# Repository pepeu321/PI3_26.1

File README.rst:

Controle de velocidade com telemetria e acionamento remoto da esteira transportadora do laboratório LPAE
#####################################################################

.. image:: imagens_principal/Esteira.png
   :width: 400px
   :align: center

.. contents::
   :local:
   :depth: 2

Visão geral
***********

Este projeto consiste no desenvolvimento de um sistema de controle de velocidade para uma esteira acionada por um motor DC, utilizando o microcontrolador ESP32. O sistema permite ao usuário definir a velocidade desejada pelo computador, enquanto um sensor realiza a medição da velocidade real do motor. Com base nessas informações, o controlador ajusta o sinal PWM aplicado ao motor, garantindo um controle preciso.

O projeto foi dividido em quatro etapas principais:

- `Etapa 1 <etapa_1/README.md>`_

Nesta etapa, foi realizado o estudo do microcontrolador ESP32, tipo do sensor que será utilizado, a comparação entre rampa de aceleração linear e rampa em S e o diagrama de blocos do sistema, permitindo a visualização geral do funcionamento do projeto.

- `Etapa 2 <etapa_2/README.rst>`_

Na Etapa 2, foram realizados testes individuais com os sensores que serão utilizados com o microcontrolador, e o desenvolvimento dos esquemáticos dos hardwares do sistema. 

- `Etapa 3 <etapa_3/README.rst>`_

Foi implementada a leitura do encoder utilizando o periférico PCNT corretamente, feito os layouts da PCI do driver que foi feito, foram desenvolvidos os firmwares responsáveis pelo acionamento do motor através do driver L298N e um programa preliminar para testar a comunicação COAP, além de fazer o projeto e implementação inicial de um controlador PID que será aplicado na esteira.

- `Etapa 4 <etapa_4/README.rst>`_

Por fim, na última etapa, foram integrados os módulos desenvolvidos nas etapas anteriores, incluindo a leitura do encoder, o acionamento do motor e a comunicação CoAP. Também foi implementado e ajustado o controlador PI, permitindo o controle de velocidade da esteira em malha fechada.
Além disso, foi desenvolvido um sistema de monitoramento remoto, capaz de definir a velocidade de referência e visualizar, em tempo real, a velocidade medida, o erro de controle, o duty cycle aplicado ao motor e o sentido de rotação.

Interface do usuário
********************

O controle remoto da esteira é realizado por uma aplicação desenvolvida em Python.

Os comandos disponíveis são:

- **on**
    Liga a esteira utilizando uma referência padrão.

- **off**
    Desliga a esteira.

- **rpm**
    Realiza uma única leitura da velocidade atual.

- **monitor**
    Exibe continuamente:

    - velocidade de referência;
    - velocidade medida;
    - erro de controle;
    - duty cycle aplicado;
    - sentido de rotação.

- **fwd**
    Define o sentido direto de rotação.

- **rev**
    Define o sentido reverso de rotação.

- **q**
    Encerra a aplicação

Diagrama de blocos do Sistema
********************

.. image:: imagens_principal/DiagramaBlocos.png
   :width: 700px
   :align: right

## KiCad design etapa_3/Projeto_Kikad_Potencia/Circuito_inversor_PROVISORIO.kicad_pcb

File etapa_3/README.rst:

Etapa 3
#######

.. contents::
   :local:
   :depth: 2

Visão geral
***********

Na Etapa 3, foram realizados 

📌 Projeto do controlador PID

📌 Implementação preliminar do controle PID no microcontrolador.

📌 Apresentação do gabinete desenvolvido em software 3D

📌 Layout da placa de potência

📌 Layout da placa de controle

📌 Teste de acionamento do motor

📌 Firmware preliminar com teste de comunicação COAP

Desenvolvimento
***************

Projeto do controlador PID
======

A primeira parte para o desenvolvimento do projeto de controle PID é a obtenção da planta do motor da esteira. Com a planta saberemos a resposta que o motor tem para uma resposta ao degrau, como é o comportamento da velocidade do motor(RPM) ao longo do tempo até atingir o regime permanente. 

Para obter a planta configuramos uma fonte de bancada com 12V e corrente limitada em 2A, depois disso é necessário conectar os pinos do encoder no esp32, como feito na etapa anterior. Com o encoder conectado ao esp32 é preciso gerar um sinal de degrau, e o degrau é gerado ligando a fonte de bancada. E para obter o gráfico da curva do rpm será preciso fazer as leituras do rpm através do esp, e então para cada instante de tempo amostrado e a leitura do rpm obtida será printada na tela. Depois copiamos esses valores para geração do gráfico no matlab.

O código anterior utilizado para medir o rpm com o encoder óptico estava certo para a configuração da etapa anterior, nesta etapa precisamos modificar o código da leitura do encoder porque no momento em que o rpm era amostrado também era printado na tela. E a função print tem um atraso, isso acarretava na perda de eventos. O rpm medido era defasado, então para velocidades que não variam até funciona, mas para obter uma curva é preciso retirar o print. E é o que foi feito.

Também foi retirada a função delay 100 ms, porque nós queremos ter uma precisão na leitura dos rpms. Para fazer isso foi necessário configurar um timer para contar até 100ms e quando chegar nesse período de tempo é gerado um sinal para calcular o rpm e armazenar em um vetor. Então depois de fazer a leitura, será printado o vetor de velocidades, com isso resolvemos o problema do print e também temos a precisão na leitura das amostras.

Então a diferença maior foi feita na main.c, o wheel.c e wheel.h não foram alterados. O código da main.c pode ser visto abaixo:

.. code-block:: c

	#include <stdio.h>
	
	#include "freertos/FreeRTOS.h"
	#include "freertos/task.h"
	
	#include "esp_log.h"
	#include "driver/gptimer.h"
	
	#include "wheel.h"
	
	static const char *TAG = "MAIN";
	
	#define PULSOS_POR_VOLTA 20
	
	#define TEMPO_TOTAL_MS     4000
	#define PERIODO_AMOSTRA_MS 100
	
	#define NUM_AMOSTRAS (TEMPO_TOTAL_MS / PERIODO_AMOSTRA_MS)
	
	static volatile bool sample_flag = false;

	// CALLBACK TIMER
	
	static bool timer_callback(
	    gptimer_handle_t timer,
	    const gptimer_alarm_event_data_t *edata,
	    void *user_ctx)
	{
	    sample_flag = true;
	    return false;
	}

	 //TIMER
	
	static gptimer_handle_t init_sample_timer(void)
	{
	    gptimer_handle_t timer = NULL;
	
	    gptimer_config_t timer_config = {
	        .clk_src = GPTIMER_CLK_SRC_DEFAULT,
	        .direction = GPTIMER_COUNT_UP,
	        .resolution_hz = 1000000,
	    };
	
	    ESP_ERROR_CHECK(
	        gptimer_new_timer(
	            &timer_config,
	            &timer));
	
	    gptimer_event_callbacks_t cbs = {
	        .on_alarm = timer_callback,
	    };
	
	    ESP_ERROR_CHECK(
	        gptimer_register_event_callbacks(
	            timer,
	            &cbs,
	            NULL));
	
	    gptimer_alarm_config_t alarm_config = {
	        .reload_count = 0,
	        .alarm_count = PERIODO_AMOSTRA_MS * 1000,
	        .flags = {
	            .auto_reload_on_alarm = true,
	        },
	    };
	
	    ESP_ERROR_CHECK(
	        gptimer_set_alarm_action(
	            timer,
	            &alarm_config));
	
	    ESP_ERROR_CHECK(gptimer_enable(timer));
	    ESP_ERROR_CHECK(gptimer_start(timer));
	
	    return timer;
	}

	// TASK AQUISICAO
	
	void task_aquisicao(void *pvParameters)
	{
	    wheel_Init();
	
	    int last_pulsos = 0;
	
	    float vetor_rpm[NUM_AMOSTRAS];
	
	    float rpm_filtrado = 0;
	
	    ESP_LOGI(TAG, "5 s");
	    vTaskDelay(pdMS_TO_TICKS(1000));
	
	    ESP_LOGI(TAG, "4 s");
	    vTaskDelay(pdMS_TO_TICKS(1000));
	
	    ESP_LOGI(TAG, "3 s");
	    vTaskDelay(pdMS_TO_TICKS(1000));
	
	    ESP_LOGI(TAG, "2 s");
	    vTaskDelay(pdMS_TO_TICKS(1000));
	
	    ESP_LOGI(TAG, "1 s");
	    vTaskDelay(pdMS_TO_TICKS(1000));
	
	    ESP_LOGI(TAG, "AGORA!");
	
	    gptimer_handle_t timer = init_sample_timer();
	
	    int n = 0;
	
	    while (n < NUM_AMOSTRAS)
	    {
	        if (sample_flag)
	        {
	            sample_flag = false;
	
	            int pulsos;
	
	            wheel_GetEncoderPulses(&pulsos);
	
	            int delta = pulsos - last_pulsos;
	
	            last_pulsos = pulsos;
	
	            float dt = PERIODO_AMOSTRA_MS / 1000.0f;
	
	            float rpm = (delta / (float)PULSOS_POR_VOLTA)* (60.0f / dt);
	
	            // filtro exponencial
	            rpm_filtrado =
	                0.7f * rpm_filtrado +
	                0.3f * rpm;
	
	            vetor_rpm[n] = rpm_filtrado;
	
	            n++;
	        }
	
	        vTaskDelay(pdMS_TO_TICKS(1));
	    }
	
	    ESP_ERROR_CHECK(gptimer_stop(timer));
	    ESP_ERROR_CHECK(gptimer_disable(timer));
	    ESP_ERROR_CHECK(gptimer_del_timer(timer));
	
	    ESP_LOGI(TAG, "Fim da aquisicao");
	
	    // CSV
	    printf("\n");
	    printf("tempo,rpm\n");
	
	    for (int i = 0; i < NUM_AMOSTRAS; i++)
	    {
	        float tempo =
	            i * (PERIODO_AMOSTRA_MS / 1000.0f);
	
	        printf("%.2f,%.2f\n",
	               tempo,
	               vetor_rpm[i]);
	    }
	
	    vTaskDelete(NULL);
	}

	void app_main(void)
	{
	    ESP_LOGI(TAG, "Sistema iniciado");
	
	    xTaskCreate(
	        task_aquisicao,
	        "task_aquisicao",
	        4096,
	        NULL,
	        5,
	        NULL);
	}

Os destaques para esse código são o tempo total de leitura, 4s, o que é mais do que suficiente para o motor atingir o regime permanente e o início da leitura é informado na tela para gerar o degrau(ligar a fonte) e então as amostras serem obtidas durante esses 4 segundos totais. O período de amostras foi definido em 100 ms, e com isso você terá um número total de amostras em 4 segundos, que está sendo feito automaticamente. Então 100 ms o número total de amostras é 40. Esse será o tamanho do vetor de velocidades capturadas. 
As capturas são feitas através de uma tarefa “task_aquisicao”, a lógica é semelhante à do código da etapa anterior. E após a leitura é printado na tela os valores de tempo e rpm para cada instante.

.. image:: Imagens/pontos_obtidos.png
   :width: 800px
   :align: center
*Figura 1  – Pontos obtidos*

*Fonte: Autoria própria*

Com os pontos obtidos utilizamos o matlab para traçar as curvas com os testes realizados.

.. image:: Imagens/curva_amostrada.jpg
   :width: 550px
   :align: center
*Figura 2  – Curva amostrada*

*Fonte: Autoria própria*

Como cada instante de tempo do início do degrau muda, porque somos nós que ligamos a fonte, foi necessário normalizar as curvas para todas iniciarem no t = 0. E com as curvas traçadas foi criada uma curva que faz a média delas, esta curva está na cor preta. 

.. image:: Imagens/Planta_motor.jpg
   :width: 800px
   :align: center
*Figura 3  – Curva de resposta da Planta do motor*

*Fonte: Autoria própria*

Essa curva média apresenta algumas inconsistências na leitura, então foi "limpada" a curva para eliminar esses valores discrepantes, como mostra a curva em vermelho da figura 3. Fizemos isto, pois a leitura do encoder no regime permanente está certa, verificamos no osciloscópio que o seu valor é 30 rpm. Na figura abaixo foi contado 10 pulsos, mas como o encoder tem 20 ranhuras, dividimos por 2 a frequência que foi obtida no osciloscópio (aproximadamente 1Hz).

.. image:: Imagens/osciloscopio.jpg
   :width: 550px
   :align: center
*Figura 4  – Frequência regime permanente(30 RPM)*

*Fonte: Autoria própria*

E Com base na resposta ao degrau apresentada na Figura 3 da curva em vermelho, o comportamento do sistema foi aproximado por um modelo de primeira ordem, dado por:

**G(s) = 2.5 / (0.291s + 1)**

Onde 2,5 representa o ganho estático K do sistema e 0,291*s a constante de tempo da planta

E com essa planta foi feita a resposta ao degrau no matlab para comparar com a curva "limpa" e a da média:

.. image:: Imagens/valid_planta.jpg
   :width: 800px
   :align: center
*Figura 5  – Resposta ao degrau final do motor*

*Fonte: Autoria própria*

E pode ser verificado que as curvas da planta "limpa" e a de resposta ao degrau coincidem. E com isso podemos começar a projetar  o controle do tipo PID.

Para o controle de velocidade do motor, será usado um controlador do tipo Proporcional-Integral (PI), devido suas características de eliminação do erro em regime permanente e simplicidade de implementação em sistemas embarcados.

O controlador PI é descrito por:
C(s) = Kp + Ki/s

Para ver a ação de controle, é necessário fechar malha e observar a resposta da curva de 2 ordem, a equação da FTMF pode ser escrita como:
FTMF = FTMD/(1+FTMA)

A simulação do sistema foi feito com o matlab, onde inicalmente foi adotado valores para Kp e KI para observar o comportamento do sistema em malha fechada, esses valores foram usados como ponto de partida para análise do sistema, para então serem ajustados na implementação do controlador.

Ajustando os valores é possível observar que o Kp (ganho proporcional) influencia diretamente na velocidade da resposta do sistema enquando o Ki (ganho integral), atua eliminando o erro em regime permanente 

.. code-block:: c

	clc; clear all
	
	pkg load control
	Gs= tf(2.5,[0.291 1])
	%step(Gs)

	% controlador PI
	Kp = 0.78;
	Ki = 6.67;
	
	Cs = tf([Kp Ki],[1 0])
	
	% malha fechada
	FTMF = Gs/(1+Gs*Cs)
	
	step(FTMF)

Equação FTMF obtida para valores de Kp e Ki de testes:

.. code-block:: c

                 0.7275 s^2 + 2.5 s
 y1:  -----------------------------------------
      0.08468 s^3 + 1.149 s^2 + 7.802 s + 16.68

Resposta ao degrau FMTF:

.. image:: Imagens/RespostaFTMF.png
   :width: 500px
   :align: center
*Figura 6  – Resposta ao degrau final do motor*

*Fonte: Autoria própria*

Implementação preliminar do controle PID no microcontrolador.
======

O controlador PI implementado possui ação proporcional para resposta rápida às variações de velocidade, ação integral para reduzir o erro em regime permanente e verificação de saturação do sinal PWM

Apresentação do gabinete desenvolvido em software 3D
======

Para a confecção do gabinete por meio de impressão 3D, fez-se necessária a
verificação das dimensões de cada placa, bem como das furações para os
parafusos de fixação. A placa de potência possui dimensões de 9 cm x 9 cm x
4 cm, enquanto a placa de controle mede 8 cm x 7 cm x 2 cm. Com base nisso,
estimou-se uma altura total de 8 cm para o gabinete, considerando os 6 cm
somados da altura das placas e 2 cm de folga distribuídos entre elas, a base e
o teto. O comprimento e a largura externos do gabinete foram fixados em 13
cm. Como cada parede possui uma espessura de 0,5 cm, a área útil interna
resultante é de 12 cm x 12 cm. A tampa e a base também foram projetadas
com espessura de 0,5 cm. No modelo, foram integradas outras formas
geométricas tridimensionais, tais como:

. Cilindros: para fixação da placa de potência e para fixação do gabinete
(pés);

. Paralelepípedos em &quot;L&quot;: para o suporte de encaixe da placa de controle;

. Paralelepípedo plano: para a composição da tampa;

. Prismas: atuando como reforços e suportes para o travamento da
tampa.

Para a criação das aberturas e detalhes por meio de operações de subtração,
utilizaram-se blocos inclinados para os rasgos de ventilação (respiros) laterais
e da base, e extrusões invertidas para a gravação em relevo de identificação
do gabinete. Vale ressaltar que todas as furações destinadas aos parafusos de
fixação foram padronizadas com diâmetro de 3 mm, utilizando cilindros como
orifícios de subtração. Conforme apresentado na Figura 6, as numerações
correspondem a:

. 1 e 2: Acessórios do gabinete (tampa e pés, respectivamente);

. 3: Gabinete completo montado;

. 4: Modelos volumétricos (simulação) das placas utilizados como
referência dimensional.

Todo o desenvolvimento do projeto 3D foi realizado no software online e
gratuito Tinkercad.

.. image:: Imagens/Gabinete-acessorio3D.png
   :width: 600px
   :align: center
*Figura 7 – Projeto do gabinete e acessórios 3D no software Tinkercad*

*Fonte: autoria própria*

O software Ultimaker Cura foi utilizado para o fatiamento dos modelos. Por
meio dele, gerou-se uma prévia dos trabalhos a serem executados na
impressora 3D Creality Ender 3 — equipamento disponível no laboratório do
IFSC e amplamente adotado no mercado de impressão 3D. Os dois trabalhos
somados (gabinete e acessórios) apresentam um tempo total estimado de
execução de aproximadamente 48 horas, devido à complexidade da geometria
e à alta densidade de preenchimento (infill) selecionada para garantir maior
robustez mecânica às peças. Este tempo de produção pode ser otimizado
reduzindo-se parâmetros como a porcentagem de preenchimento e perímetros.
Como a confecção física do gabinete e de seus acessórios ficará a cargo da
Etapa IV, a definição final desses parâmetros de impressão — bem como a
avaliação de possíveis reduções na altura do gabinete — será decidida
futuramente. A prévia do fatiamento realizado no Ultimaker Cura pode ser
visualizada na Figura 7, disposta da esquerda para a direita com o gabinete e
seus respectivos acessórios.

.. image:: Imagens/PreVisu3D.png
   :width: 500px
   :align: center
*Figura 8 - Visualização 3D e esquema de furação*

*Fonte: autoria própria*

Layout da placa de potência
======

O layout da placa de circuito impresso (PCI) foi desenvolvido no Kicad 10, com os componentes importados diretamente do esquemático criado na Etapa II. O posicionamento dos componentes, as trilhas de conexão e as áreas de plano foram baseados na placa de teste (demoboard) recomendada na documentação da fabricante Infineon para o driver meia-ponte BTN8982TA. O layout de referência e a respectiva placa física finalizada são apresentados conforme a Figura 1 da esquerda para direita como: top layer, bottom layer e demoboard.

.. image:: Imagens/LayoutDemo.png
   :width: 600px
   :align: center
*Figura 9 – Layout da placa de demonstração para o BTN8982TA*

*Fonte: Adaptado de Infineon Technologies AG (2011)*

Observa-se uma largura significativa nas trilhas de potência, projetadas para suportar correntes contínuas de até 55A. Essa largura é de 20mm por camada com espessura de cobre de 4oz/ft² total, totalizando uma seção transversal equivalente a 40mm de largura combinada. No protótipo desenvolvido (Figura 2), manteve-se a largura combinada de 40mm, porém com espessura restrita a 2oz/ft² somando ambas as faces, devido às limitações de matéria-prima disponíveis no IFSC. 

A validação dimensional foi realizada por meio de cálculos baseados na norma IPC-2221. Embora a largura nominal atenda aos critérios na maior parte da extensão, o layout inevitavelmente apresenta estreitamentos geométricos e reduções na área de condução próximos aos terminais do componente. Para mitigar o surgimento de pontos quentes (hotspots) nesses gargalos e proteger o substrato de fenolite, cuja temperatura de transição vítrea e a resistência térmica são substancialmente inferiores às do padrão FR-4 recomendado —, previu-se a remoção da máscara de solda ao longo das trilhas de potência para a aplicação de uma camada de estanho adicional. Essa técnica reduz a resistência ôhmica equivalente e melhora a dissipação térmica do circuito. 

Por fim, ressalta-se que foram realizadas alterações pontuais em relação ao projeto original da demoboard, tais como a remoção de conectores auxiliares redundantes e a substituição de componentes SMD por equivalentes PTH (Through-Hole). Essa decisão de projeto justificou-se pela necessidade de otimizar o processo de confecção manual local do protótipo e facilitar futuras manutenções corretivas em laboratório, sem comprometer a integridade e o funcionamento do circuito. A placa desenvolvida pode ser vista conforme a Figura 2, da esquerda para a direita como: top layer e bottom layer.

.. image:: Imagens/LayoutPCB_Pot.png
   :width: 450px
   :align: center
*Figura 10 - Layout da placa desenvolvida*

*Fonte: Autoria própria*

O circuito foi projetado para operar com uma corrente contínua de 35A sob tensão nominal de 24V, totalizando uma capacidade de potência de até 840W. De acordo com os critérios de isolamento para a faixa de 0V a 30V CC, o distanciamento mínimo (clearance) entre as trilhas deve ser de aproximadamente 0,13mm, validando a segurança operacional do protótipo nesta faixa de tensão. A confecção da placa seguiu estritamente os parâmetros técnicos recomendados pelo manual de desenvolvimento para fresa mecânica do IFSC, cujas especificações de fabricação estão detalhadas na Tabela 1. Para o dimensionamento térmico das trilhas de potência, os cálculos baseados na norma IPC-2221 resultaram em uma largura recomendada de 677 mil (aproximadamente 17,2mm, arredondados para 20mm no layout), considerando uma elevação de temperatura limite de 40°C em relação ao ambiente. A interface da ferramenta utilizada para essa validação é apresentada na Figura 3.

.. image:: Imagens/Calc_trilha.png
   :width: 250px
   :align: center
*Figura 11 – Ferramenta de cálculo de largura de trilha IPC-2221*

*Fonte: Altium (2025)*

Configurações da placa desenvolvida:

+-----------------------------------+------------------+
| Parâmetro                         | Valor            |
+===================================+==================+
| Isolamento entre trilhas          | 8 mil            |
+-----------------------------------+------------------+
| Isolamento entre borda e cobre    | 12 mil           |
+-----------------------------------+------------------+
| Isolamento de furo a furo         | 16 mil           |
+-----------------------------------+------------------+
| Largura mínima de trilha          | 20 mil           |
+-----------------------------------+------------------+
| Diâmetro mínimo de furo           | 40 mil           |
+-----------------------------------+------------------+
| Diâmetro mínimo de cobre          | 80 mil           |
+-----------------------------------+------------------+
| Camada de cobre                   | 1 oz/ft²         |
+-----------------------------------+------------------+
*Tabela 1 – Configurações da placa desenvolvida*

*Fonte: Autoria própria*

Para a fabricação por fresa mecânica, é indispensável a geração dos arquivos em formato Gerber, os quais mapeiam com precisão as coordenadas de furação, o dimensionamento das trilhas e as distâncias de isolamento. Estes arquivos foram exportados e serão encaminhados ao técnico responsável pelo setor de fresa durante a Etapa IV para a execução da usinagem. Uma pré-visualização tridimensional do circuito, simulada no ambiente Kicad, é apresentada da esquerda para direita na Figura 4, como: top layer e bottom layer. Após a entrega da placa física, os componentes listados na Tabela 2 serão soldados para que o protótipo seja submetido aos testes de validação, procedimentos que também integrarão o escopo da Etapa IV.

.. image:: Imagens/Visu3D.png
   :width: 400px
   :align: center
*Figura 12  – Pré-visualização do trabalho no software Ulti Maker*

*Fonte: autoria própria*

Lista de componentes:

+----------------+----------------------+-------------------------------------------+
| Tipo           | Quantidade           | Valor                                     |
+================+======================+===========================================+
| Resistores     | 2x, 2x, 5x           | 1 kΩ, 5,1 kΩ@1%, 10 kΩ                    |
+----------------+----------------------+-------------------------------------------+
| Capacitores    | 2x, 5x, 4x, 1x       | 1nF, 100nF, 220nF, 1000uF (low ESR)       |
+----------------+----------------------+-------------------------------------------+
| Semicondutores | 2x, 1x, 1x           | BTN8982TA, IPD90P03P4L04, Diodo 10V@1W    |
+----------------+----------------------+-------------------------------------------+
| Conectores     | 4x, 1x               | Furo AWG8, Molex 5 pinos                  |
+----------------+----------------------+-------------------------------------------+
| Total          | 25                   |                                           |
+----------------+----------------------+-------------------------------------------+
*Tabela 2 – Lista de componentes*

*Fonte: autoria própria*

Layout da placa de controle
======

Inicialmente, cogitou-se o desenvolvimento de uma segunda placa de circuito impresso dedicada exclusivamente aos circuitos de controle, de modo a isolá-los fisicamente da etapa de potência. Contudo, devido à relativa simplicidade do circuito de controle e mediante o aval do corpo docente, optou-se pela utilização de uma placa adaptadora comercial para o ESP32 dotada de terminais de saída. A integração dessa solução justificou-se pelo fato de o módulo comercial possuir padrão de fabricação industrial, o que confere elevada robustez e confiabilidade elétrica ao sistema. Desse modo, evitou-se a replicação manual de um circuito integrado cujas especificações de qualidade em laboratório não igualariam o padrão industrial disponível. 
O diagrama completo das interconexões do sistema é apresentado na Figura 5, ilustrando, da esquerda para a direita, a placa adaptadora e o respectivo diagrama esquemático.

.. image:: Imagens/PCB-Controle.png
   :width: 500px
   :align: center
*Figura 13 – Esquema de conexões da placa de controle*

*Fonte: autoria própria*

Teste de acionamento do motor
======

Para testar o acionamento do motor da esteira, foi desenvolvido um firmware responsável pela geração do sinal PWM, controle do driver e aquisição da velocidade utilizando o encoder acoplado ao eixo do motor.

Para a parte de leitura e aquisição da velocidade em RPM, foi utilizado como base o código desenvolvido anteriormente para o encoder, reutilizando o módulo “wheel”. Porém, a forma de aquisição dos dados foi alterada para melhorar a medição em baixas velocidades, já que para valores baixos de RPM a quantidade de pulsos gerados pelo encoder em pequenos intervalos de tempo é reduzida, tornando a leitura sensível, mostrando valores falsos.

Para fins de teste e validação do acionamento, foi utilizado o driver L293N. Apesar de não ser o driver mais adequado para o motor da esteira (BDC - Brushed DC Motor), ele permitiu validar o funcionamento do acionamento inicial do sistema. O L293N possui limitação de tensão máxima em torno de 12V e apresenta uma queda de tensão significativa internamente, normalmente entre 2V e 4V. O motor da esteira, por outro lado, é capaz de operar com até 24V, valor no qual atingiria sua velocidade máxima nominal.

.. image:: Imagens/L298N.jpg
   :width: 450px
   :align: center
*Figura 14 – Módulo driver L298N*  

*Fonte: Components101*

No firmware foi desenvolvido o módulo “Motor”, que utiliza o periférico LEDC para geração do PWM. Foi configurado com frequência de 1 kHz e resolução de 10 bits, permitindo um duty cycle na faixa de 0 a 1023. 

Conexões:

GPIO14  → D0 encoder

GPIO18  → ENB LF293N (PWM)

GPIO2    → IN3 LF293N (Sentido)

GPIO21  → IN4 LF293N (Sentido)

O timer do PWM foi criado com a estrutura ledc_timer_config_t, ele foi configurado com uma frequência de 1kHz e uma resolução de 10bits, o que dá uma faixa para o PWM de 0 a 1023.
Para validar foram realizadas medições com o osciloscópio tanto na saída PWM do microcontrolador quanto na saída do driver conectada ao motor. 

A Figura  mostra o sinal PWM medido na saída do microcontrolador. Possui um sinal PWM com frequência aproximada de 1 kHz e amplitude próxima de 3,3V, que corresponde com o esperado.

.. image:: Imagens/PWM-Micro.PNG
   :width: 450px
   :align: center
*Figura 15 - Sinal PWM gerado microcontrolador*

*Fonte : Autoria própria*

O sinal medido na saída do driver conectado ao motor da esteira é mostrado na figura abaixo. Ele reproduz o PWM aplicado, com uma amplitude maior, algumas deformações e quedas de tensão características do L293N.

.. image:: Imagens/Saida_Driver.PNG
   :width: 450px
   :align: center
*Figura 16 - Sinal na saída do driver*

*Fonte : Autoria própria*

A função motor_SetDuty(), foi feita para alterar o valor do duty cycle, fazendo com que a tensão média aplicada no motor varie, e como consequência a velocidade.
Foram feitos diversos testes alterando o PWM e o sentido da esteira, e visivelmente a velocidade se alterava, no terminal, imprimia a velocidade atual com uma certa variação, não sendo possível dectectar uma velocidade especifica e sim uma faixa.

O modelo teórico utilizado para estimar a velocidade do motor foi baseado na relação entre a tensão média aplicada e a velocidade angular, sendo aproximado por:

RPM ≈ 37 · (D − 0.33)

Onde D representa o duty cycle normalizado (PWM/1023), o modelo considera a existência de uma tensão mínima necessária para iniciar o movimento do motor, representada pelo termo de offset.

Comparação entre RPM teórico e medições práticas

+------+--------+--------------+----------------------+------------------------+
| PWM  | Duty   | RPM Teórico  | RPM Médio (Prático)  | Faixa (Min – Max)      |
+======+========+==============+======================+========================+
| 350  | 0.34   | ~0           | 0                    | Não acionou            |
+------+--------+--------------+----------------------+------------------------+
| 550  | 0.54   | ~7.8         | ~9.5                 | 6.48 – 12.54           |
+------+--------+--------------+----------------------+------------------------+
| 750  | 0.73   | ~15.0        | ~14.8                | 10.50 – 18.97          |
+------+--------+--------------+----------------------+------------------------+
| 950  | 0.93   | ~22.2        | ~19.8                | 17.34 – 21.82          |
+------+--------+--------------+----------------------+------------------------+
| 1023 | 1.00   | ~25.0        | ~23.5                | 21.36 – 26.02          |
+------+--------+--------------+----------------------+------------------------+
*Tabela 3 - Comparação de valores*

*Fonte : Autoria própria*

A partir dos resultados, foi observado uma zona morta para valores próximo a 33% (PWM = 350), onde o motor não consegue ser acionado. Para baixos valores como em PWM = 550, a leitura da velocidade varia bastante, devido ao erro de leitura para baixas velocidades.

Para valores de PWM maiores ou a 750, o sistema apresenta um comportamento próxmio de linear, além de que os valores não variam tando, tendo dado bem próximo do teórico.

Por fim, o teste em sentido reverso, realizado com PWM máximo, confirmou o correto funcionamento do controle de direção, apresentando valores de velocidade compatíveis com o acionamento direto

Firmware preliminar com teste de comunicação COAP
======

.. code-block:: c

    #include <stdio.h>
    #include <string.h>

    #include "freertos/FreeRTOS.h"
    #include "freertos/task.h"

    #include "esp_wifi.h"     //controla wifi
    #include "esp_event.h"    //sitema de eventos do esp
    #include "esp_log.h"

    #include "lwip/sockets.h" // sockets UDP/TCP
    #include "lwip/netdb.h"
    #include "lwip/inet.h"    // IP e portas

    #include "nvs_flash.h"    //Memória flash usada pelo Wi-Fi
    #include "esp_netif.h"    //Camada de interface de rede

    #include "coap3/coap_forward_decls.h"
    #include "coap3/coap.h" //biblioteca COAP

    #define WIFI_SSID "lpae_wifi"
    #define WIFI_PASS "esp-8266"

    static bool coap_task_started = false;  //flag para ver se a tarefa nao fica se repetindo,criando varias vezes
    static const char *TAG = "WIFI";
    static int velocidade_atual = 0;        //variavel que é o estado atual da esteira

    //função que será chamada AUTOMATICAMENTE quando chegar: POST /vel
    //deixa o esp como servidor COAP, capaz de receber comando externo
    void hnd_post_vel(
        coap_resource_t *resource, //recurso coap acessado (/vel)
        coap_session_t *session,   //sessao COAP de quem enviou a mensagem
        const coap_pdu_t *request, //Pacote que chega no esp
        const coap_string_t *query,
        coap_pdu_t *response)      //Pacote de resposta que o esp vai devolver
    {
        size_t size;     //numero de bytes que chega
        uint8_t *data;   //ponteiro para os bytes que chegam

    //extrai payload recebido.
        if(coap_get_data(request, &size, &data))
        {
            ESP_LOGI(TAG, "Payload recebido no POST");

         //   printf("%.*s\n", (int)size, data);   //imprimi payload
         char buffer[20];   //cria string temporaria

        memcpy(buffer, data, size); //copia os bytes recebidos
        buffer[size] = '\0';        //transforma os bytes em string valida terminada em \0, para usar o atoi

        velocidade_atual = atoi(buffer); //atoi converte para inteiro

        ESP_LOGI(TAG, "Velocidade recebida: %d", velocidade_atual);
        }

        //define o status da resposta CoAP
        coap_pdu_set_code(response, COAP_RESPONSE_CODE_CHANGED); //envia resposta 2.04 Changed/resposta do servidor e que foi alterado alguma coisa
        const char *resp_str = "OK"; //esp respondendo ao servidor que payload foi recebido

        //coloca dentro do pacote de resposta
        coap_add_data(
            response,
            strlen(resp_str),
            (const uint8_t *)resp_str);
    }

    void hnd_get_vel(                 //cria handler GET, notebook pode pegar velocidade atual
        coap_resource_t *resource,    //recurso logico /vel
        coap_session_t *session,
        const coap_pdu_t *request,
        const coap_string_t *query,
        coap_pdu_t *response)
    {
        char resp[50];

    //monta a string "dinamica"
        sprintf(resp,
                "Velocidade atual: 8");

    //define o status da resposta CoAP
        coap_pdu_set_code(
            response,
            COAP_RESPONSE_CODE_CONTENT);

    //coloca dentro do pacote de resposta
        coap_add_data(
            response,
            strlen(resp),
            (const uint8_t *)resp);

        ESP_LOGI(TAG, "GET /vel respondido");
    }

    void coap_client_task(void *pvParameters)
    {
        ESP_LOGI(TAG, "CoAP task iniciou");

        coap_startup(); //inicializa biblioteca coap (libcoap)

        ESP_LOGI(TAG, "Biblioteca CoAP inicializada");

    //estrutura necessaria para contexto COAP(gerenciador de sessões,controle de sockets CoAP)
        coap_context_t *ctx = coap_new_context(NULL); //ctx eh "Sistema operacional do COAP"
        if(ctx == NULL)  //checa se criou contexto
        {
            ESP_LOGE(TAG, "Erro ao criar contexto CoAP");
            vTaskDelete(NULL);
            return;
        }
        ESP_LOGI(TAG, "Contexto CoAP criado");

    //Criacao do servidor
        coap_address_t serv_addr;  //cria estrutura do endereço do servidor.
        coap_address_init(&serv_addr);   //zera/inicializa estrutura.
        serv_addr.addr.sin.sin_family = AF_INET;  //usa IPv4.
        serv_addr.addr.sin.sin_addr.s_addr = INADDR_ANY;  // INADDR_ANY significa escutar qualquer IP do ESP
        serv_addr.addr.sin.sin_port = htons(5683); //abre porta padrão CoAP(5683):

        coap_endpoint_t *endpoint;  //cria o endpoint servidor CoAP/abre o socket servidor.
        endpoint = coap_new_endpoint(  //abre o “socket CoAP servidor”.
            ctx,               //contexto CoAP criado antes.
            &serv_addr,   //serv_addr é a estrutura do endereço do servidor
            COAP_PROTO_UDP);       // CoAP usa UDP.

            if(endpoint == NULL)  //testa se endpoint foi criado
        {
            ESP_LOGE(TAG, "Erro ao criar endpoint CoAP");
            vTaskDelete(NULL);
            return;
        }
        ESP_LOGI(TAG, "Endpoint servidor CoAP criado");

        //Cria recurso = "endpoint logico"
        coap_resource_t *resource;
        resource = coap_resource_init(
            coap_make_str_const("vel"), //cria endpoint vel
            0);

        coap_register_handler(  //Liga POST ao handler
    //quando chegar POST /vel  chama hnd_post_vel())
            resource,
            COAP_REQUEST_POST,
            hnd_post_vel);

        coap_register_handler(  //Liga GET ao handler
            resource,
            COAP_REQUEST_GET,
            hnd_get_vel);

        //adiciona recurso ao servidor, servidor COAP conhece "/vel "
        coap_add_resource(ctx, resource);  //Adiciona ao servidor(endpoint conhece /vel)
        ESP_LOGI(TAG, "Recurso /vel criado");

        while (1)
        {
           coap_io_process(ctx, COAP_IO_WAIT); //coap_io_process é o que faz tudo rodar
           vTaskDelay(pdMS_TO_TICKS(100));
        }
    }

    static void wifi_event_handler(             //reage a eventos do Wi-Fi.
        void *arg,
        esp_event_base_t event_base,            //qual “categoria” do evento aconteceu,IP ou WIFI.
        int32_t event_id,                       //qual evento específico aconteceu
        void *event_data)                       //dados extras do evento(IO,mascara,gateway)

    {
        // verifica se Wi-Fi iniciou com WIFI_EVENT_STA_START
        if(event_base == WIFI_EVENT &&
           event_id == WIFI_EVENT_STA_START) //quando esp liga, gera o envento WIFI_EVENT_STA_START
        {
            esp_wifi_connect();     //manda o ESP conectar no roteador.
        }

        // Conectou e recebeu IP com IP_EVENT_STA_GOT_IP
        if(event_base == IP_EVENT &&
           event_id == IP_EVENT_STA_GOT_IP)
        {
            ip_event_got_ip_t *event =
                (ip_event_got_ip_t *) event_data;        //pega IP recebido

            ESP_LOGI(TAG,
                     "IP: " IPSTR,
                     IP2STR(&event->ip_info.ip));

            if(!coap_task_started)           //garante que tarefa COAP nao seja criada varias vezes, caso a internet caia,troca IP,etc
            {
                coap_task_started = true;

                xTaskCreate(                     // cria tarefa do coap_client_task
                    coap_client_task,
                    "coap_client",
                    8192,
                    NULL,
                    5,
                    NULL);
            }
        }

        // Desconectou
        if(event_base == WIFI_EVENT &&
           event_id == WIFI_EVENT_STA_DISCONNECTED)
        {
            ESP_LOGI(TAG, "Reconectando...");
            esp_wifi_connect();
        }
    }

    void wifi_init_sta(void)    //função que monta toda infraestrutura de rede.
    {
        // Inicializa pilha de rede
        esp_netif_init();

        // Event loop, cria sistema de enventos
        esp_event_loop_create_default();

        // Cria a interface Wi-Fi no modo station
        esp_netif_create_default_wifi_sta();

        //Cria estrutura de configuração padrão do driver Wi-Fi
        wifi_init_config_t cfg =
            WIFI_INIT_CONFIG_DEFAULT();

        esp_wifi_init(&cfg);   //Inicializa driver Wi-Fi do esp

        // Registra eventos de wi-fi, qunado acontece alguma evento WIFI, chama função do evento
        esp_event_handler_instance_register(
            WIFI_EVENT,
            ESP_EVENT_ANY_ID,
            &wifi_event_handler,
            NULL,
            NULL);

        // Registra eventos de IP
        esp_event_handler_instance_register(
            IP_EVENT,
            IP_EVENT_STA_GOT_IP,
            &wifi_event_handler,
            NULL,
            NULL);

        // config do wifi
        wifi_config_t wifi_config = {
            .sta = {
                .ssid = WIFI_SSID,
                .password = WIFI_PASS
            },
        };

        esp_wifi_set_mode(WIFI_MODE_STA);  //Modo estação

        esp_wifi_set_config(                   //Aplica config
            WIFI_IF_STA,
            &wifi_config);

        esp_wifi_start();         //inicia wifi
    }

    void app_main(void)
    {
        // Inicializa NVS
        nvs_flash_init();      //Inicializa NVS(memória flash usada pelo Wi-Fi

        // Inicializa Wi-Fi
        wifi_init_sta();
    }

Nesta etapa do projeto foi desenvolvido um sistema de comunicação utilizando o protocolo CoAP com objetivo de fazer com que o microcontrolador envie e receba mensagens do servidor, que posteriormente será adptado, para conseguir acompanhar a velocidade atual da esteira e setar uma nova velocidade desejada. 

Inicialmente foi feita a configuração da conexão wi-fi em modo Station (WIFI_MODE_STA). Foram utilizados os módulos: esp_wifi, esp_event e esp_netif. A conexão foi feita usando os eventos do sistema, fazendo com que o esp: inicializasse automaticamente o wifi, conectasse ao roteador, pega o endereço IP, e caso perca o sinal, seja capaz de se reconectar.

Com o esp conectado, apereceu no terminal o IP obtido, comprovando a conexão.

Antes de implementar o COAP em si, foi feito um teste usando comunicação UDP pura, onde foi criado uma tarefa,  responsável pela criação do socket UDP, e envio de uma mensagem para um notebook conectado na mesma rede, com o objetivo de compreender melhor o protocolo, e validar a comunicação wifi e o envio de dados usando sockets UDP. A mensagem foi enviada usando a função "sendto()"

Com essa comunicação validada, foi adicionada a bbilbioteca "libcoap", que é a responsável pela implementação do protocolo. A implementação foi feita através do arquivo "idf_component.yml" e adicionada na pasta do projeto. 

Com a biblioteca adicionada, foi feito a criação da tarefa principal "coap_client_task()", responsável por inicializar a biblioteca CoAP utilizando coap_startup() e criar o contexto principal do protocolo pela da função coap_new_context(NULL). Esse contexto é o núcelo da comunicação COAP, responsável pelo gerenciamento de sessões, sockets e processar as mensagens.

Em seguida foi implementado um servidor CoAP local dentro do ESP32-S3. Para isso foi criada uma estrutura de endereço utilizando coap_address_t, configurada para utilizar IPv4 (AF_INET), protocolo UDP e a porta padrão do CoAP (5683). O servidor foi então criado utilizando a função coap_new_endpoint(), permitindo que outros dispositivos da rede enviassem requisições diretamente para o ESP.

Com o servidor criado, foi implementado o recurso "/vel", que vai representar uma URI responsável pelo controle e monitoramento da velocidade da esteira. Foi criado com coap_resource_init() e adicionado ao contexto COAP, pela função coap_add_resource().

Para tratar as requisições foi implementado dois handlers: hnd_post_vel() e hnd_get_vel().

A função post, é exectuada quando o esp receber uma mensagem no recusro /vel, ela vai extrair o payload enviado pelo cliente, extrair os dados com coap_get_data() , converter os bytes em string e transformar em inteiro. Após receber e processar o valor, o esp envia uma resposta ao client com "OK", indicando o recebimento da mensagem.  

Para hnd_get_value, foi implementada para que quando o notebook realiza um GET no recurso /vel, o ESP monta uma string contendo o estado atual da variável velocidade e envia essa informação de volta ao cliente CoAP

Para manter o funcionamento continuo foi feito um laço com a função coap_io_process(ctx, COAP_IO_WAIT), essa função é responsável por processar continuamente os eventos da pilha CoAP, como recebimento de requisições, envio de respostas e gerenciamento do protocolo.

Para validar o funcionamento, foi criado um cliente CoAP em Python utilizando a biblioteca aiocoap. O programa em Python atua como cliente da aplicação, permitindo enviar requisições POST para alterar a velocidade da esteira e requisições GET para consultar o valor atual armazenado no ESP32-S3.

.. code-block:: python

   from aiocoap import *    #implementa o protocolo CoAP em Python
   import asyncio		 #sistema assíncrono do Python

   async def main():        #cria funcao assincrona, para usar o await

   protocol = await Context.create_client_context()    #cria o cliente CoAP

   while True:

   #Post
        vel = input("Digite a velocidade: ")

        request = Message(      #cria uma requisição Post
            code=POST,		#defini o tipo(post)
            payload=vel.encode(),  #converte string em bytes
            uri="coap://192.168.1.119/vel"   #destino
        )
	
	#Envia requisição e espera resposta do esp com ok
        response = await protocol.request(request).response

        print("Resposta do ESP que recebeu:")
        print(response.payload.decode())  #converte dnv bytes em string

   #GET
        request_get = Message(     #cria uma requisição GET
            code=GET,
            uri="coap://192.168.1.119/vel"
        )

        response_get = await protocol.request(request_get).response

        print("Resposta GET:")
        print(response_get.payload.decode())

    asyncio.run(main())

No cliente Python, o usuário digita a velocidade desejada pelo prompt. O valor é convertido para bytes e enviado ao ESP através de uma requisição POST direcionada para a URI coap://IP_DO_ESP/vel. 
Em seguida, o programa Python realiza automaticamente uma requisição GET para o mesmo recurso /vel, recebendo do ESP a velocidade atual e imprimindo no mesmo prompt de comando

.. image:: Imagens/PromptCOAP.png
   :width: 600px
   :align: center
*Figura 17 - Prompt, cliente*

*Fonte : Autoria própria*

.. image:: Imagens/TerminalCOAP.png
   :width: 600px
   :align: center
*Figura 18 - Terminal esp-idf*

*Fonte : Autoria própria*

Referências (links/datasheets/livros)
*************************************

INFINEON TECHNOLOGIES AG. NovalithIC™ H-Bridge Demo Board: Version 2.2 (BTN89xxTA) – Demo Board Description. Munich: Infineon Technologies AG, 2011. Disponível em: https://www.infineon.com/assets/row/public/documents/10/57/novalithic-demoboard-v2.2-h-bridge-btn89xxta-2011-09-23.pdf. Acesso em: 27 maio 2026.

ALTIUM. IPC-2221 Calculator for PCB Trace Current and Heating. Altium Resources, 26 jun. 2025. Disponível em: https://resources.altium.com/p/ipc-2221-calculator-pcb-trace-current-and-heating. Acesso em: 27 mai. 2026.

ESPRESSIF SYSTEMS. ESP-IDF Programming Guide. Disponível em: https://docs.espressif.com/projects/esp-idf/en/latest/esp32s3/

LIBCOAP PROJECT. libcoap GitHub Repository. GitHub. Disponível em: https://github.com/obgm/libcoap

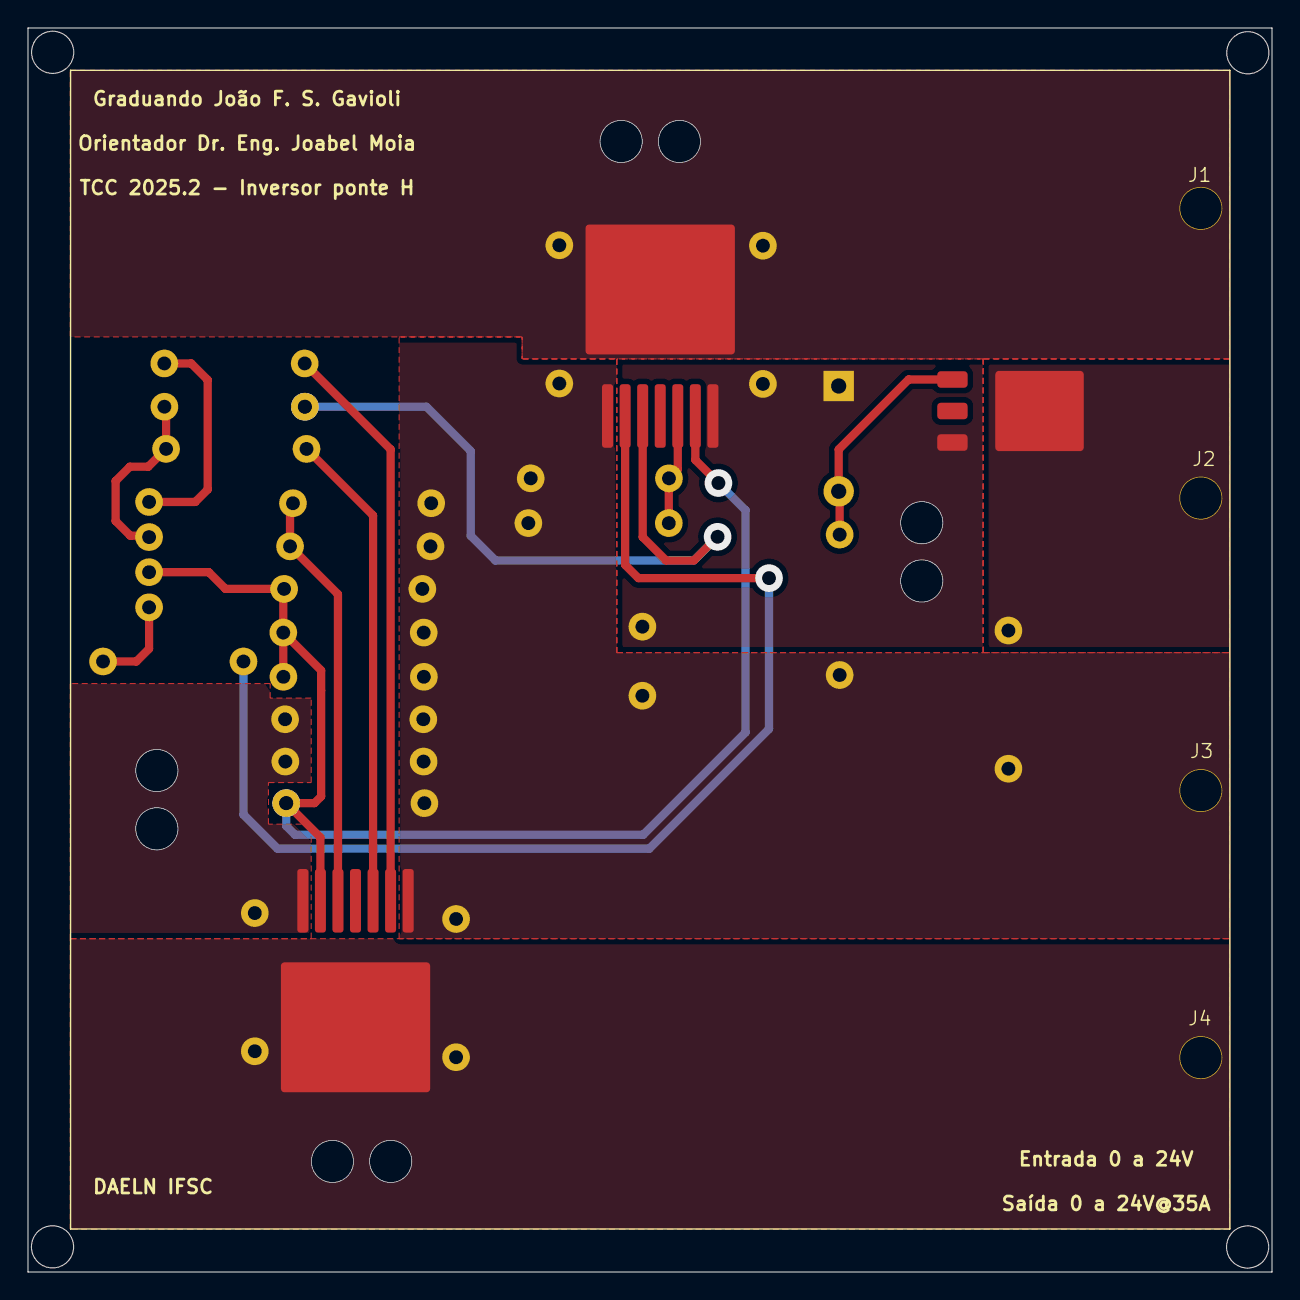
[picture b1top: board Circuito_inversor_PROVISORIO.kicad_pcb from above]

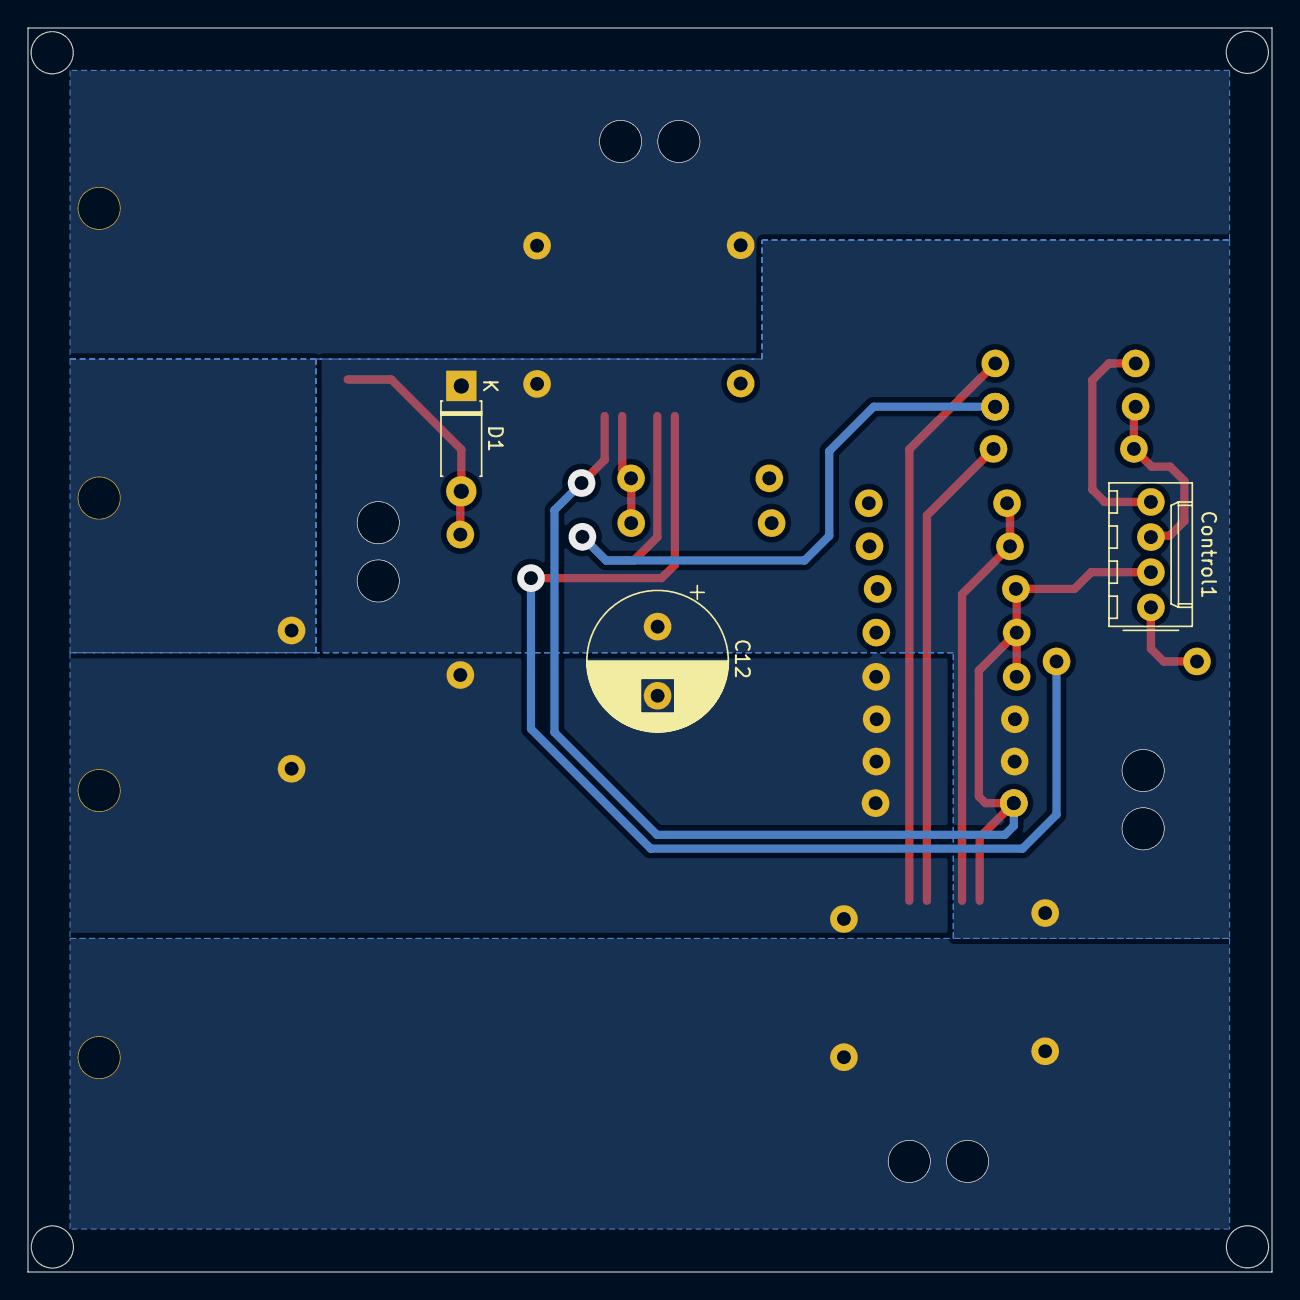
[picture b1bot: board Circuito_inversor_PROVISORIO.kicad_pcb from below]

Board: 2 copper layers, 90.0 x 90.0 mm, 30 parts (23 on the bottom side), 16 nets.

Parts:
C1, C2: 1nF; Cap_Not_Polarized_Pitch_10mm_TESTE
C3, C4, C5, C6, C7: 100nF; Cap_Not_Polarized_Pitch_10mm_TESTE
C8, C9, C10, C11: 220nF; Cap_Not_Polarized_Pitch_10mm_TESTE
C12: 1000uF; CAP_ELEC_LOW_ESR
Control1: Conn_01x04; PWM
D1: 10v@1W; D_DO-41_SOD81_P7.62mm_Horizontal
J1, J2, J3, J4: Conn_01x01; ILHA_AWG8
Q1, Q2: BTN8982TA; BTN8982TA_TESTE
Q3: IPD90P03P4L-4; IPD90P03P4L-04_TESTE
R1, R2: 1k; Resistor_0.25W_TESTE
R3, R4: 5k1; Resistor_0.25W_TESTE
R5, R6, R7, R8, R9: 10k; Resistor_0.25W_TESTE

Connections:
/Vs: C4.1, C5.1, C8.1, C10.1, C12.1, D1.1 (K), Q1.7, Q2.7, Q3.1 (D)
GND: C1.2, C2.2, C3.2, C4.2, C5.2, C6.2, C7.2, C9.2, C11.2, C12.2, J3.1, Q1.1, Q2.1, R1.2, R2.2, R3.2, R4.2, R9.2
unnamed: Control1.1, R5.1
unnamed: C1.1, C2.1, Control1.2, Q1.6 (IS), Q2.6 (IS), R1.1, R2.1
unnamed: Control1.3, R6.1, R7.1
unnamed: Control1.4, R8.2
unnamed: D1.2 (A), Q3.2 (G), R9.1
unnamed: Q1.2 (IN), R5.2
unnamed: Q1.3 (INH), R6.2
unnamed: C3.1, Q1.5 (SR), R3.1
unnamed: Q2.2 (IN), R8.1
unnamed: Q2.3 (INH), R7.2
unnamed: C6.1, Q2.5 (SR), R4.1
Vin: C7.1, J2.1, Q3.3 (S)
Vout+: C8.2, C9.1, J1.1, Q1.4, Q1.8
Vout-: C10.2, C11.1, J4.1, Q2.4, Q2.8

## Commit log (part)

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2026-04-02 Update README with additional references
    Added references for encoders and soft starters.
2026-04-02 Fix typo in motor driver description in README
2026-04-02 Simplify development section in README
    Removed redundant text about implementation details and testing.
2026-04-30 Create Imagens
2026-04-30 Create Datasheets
2026-05-26 Create Code_Resposta_Fonte
2026-05-28 Update README with cabinet design details
    Detailed the design and specifications of the 3D printed cabinet and its components, including dimensions, materials, and software used for modeling and slicing.
2026-05-29 Adjust PI controller parameters and feedback formula
    Updated PI controller gains and modified feedback calculation.
2026-05-29 Adjust image width for FMTF response
    Updated image width for FMTF response in README.
